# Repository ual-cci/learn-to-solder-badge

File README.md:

# Learn to Solder Badge

You can find out more about the CCI learn to solder baadge at [cci.to/badge](https://cci.to/badge).

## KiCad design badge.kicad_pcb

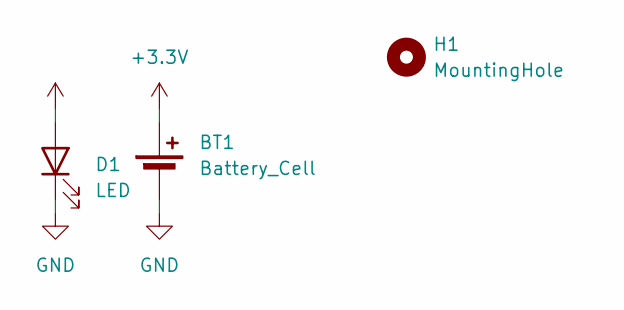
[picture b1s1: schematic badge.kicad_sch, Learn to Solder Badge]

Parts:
BT1: Battery_Cell; Clean CR2032 Holder Footprint
D1: LED; LED_D5.0mm
H1: MountingHole; MountingHole_2mm

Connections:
+3.3V: BT1.1 (+), D1.2 (A)
GND: BT1.2 (-), D1.1 (K)

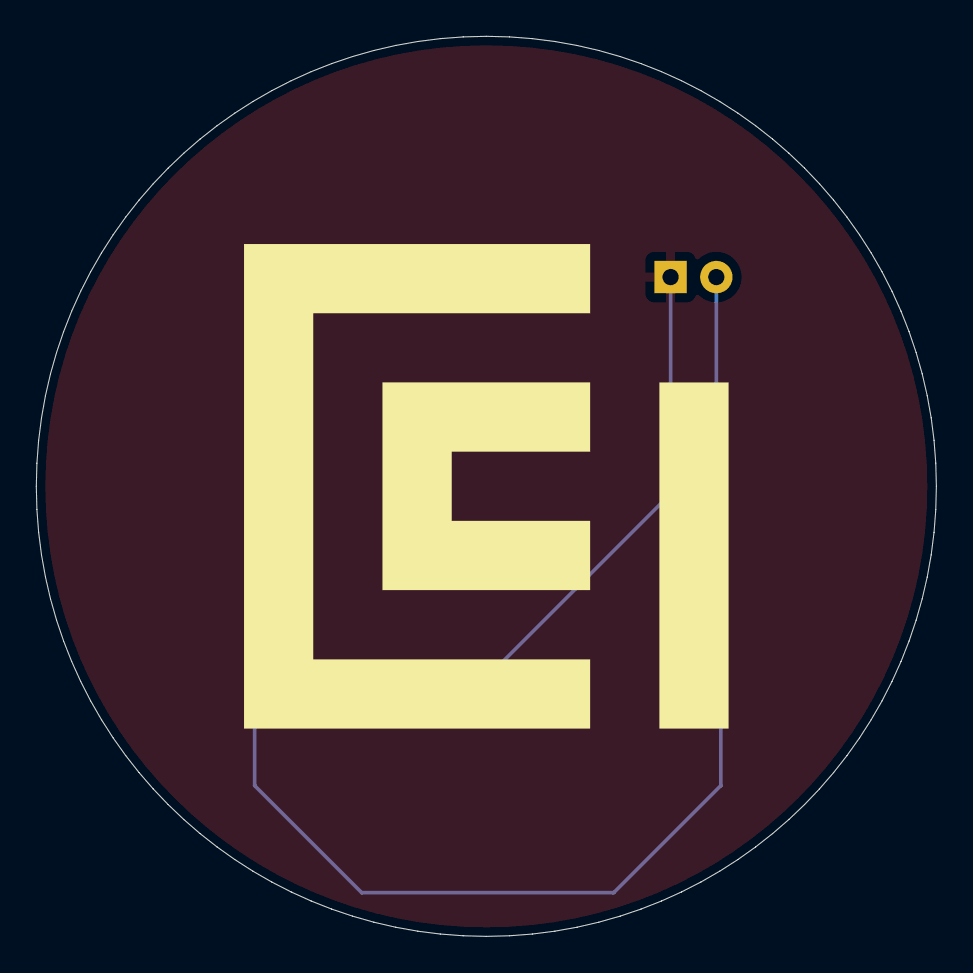
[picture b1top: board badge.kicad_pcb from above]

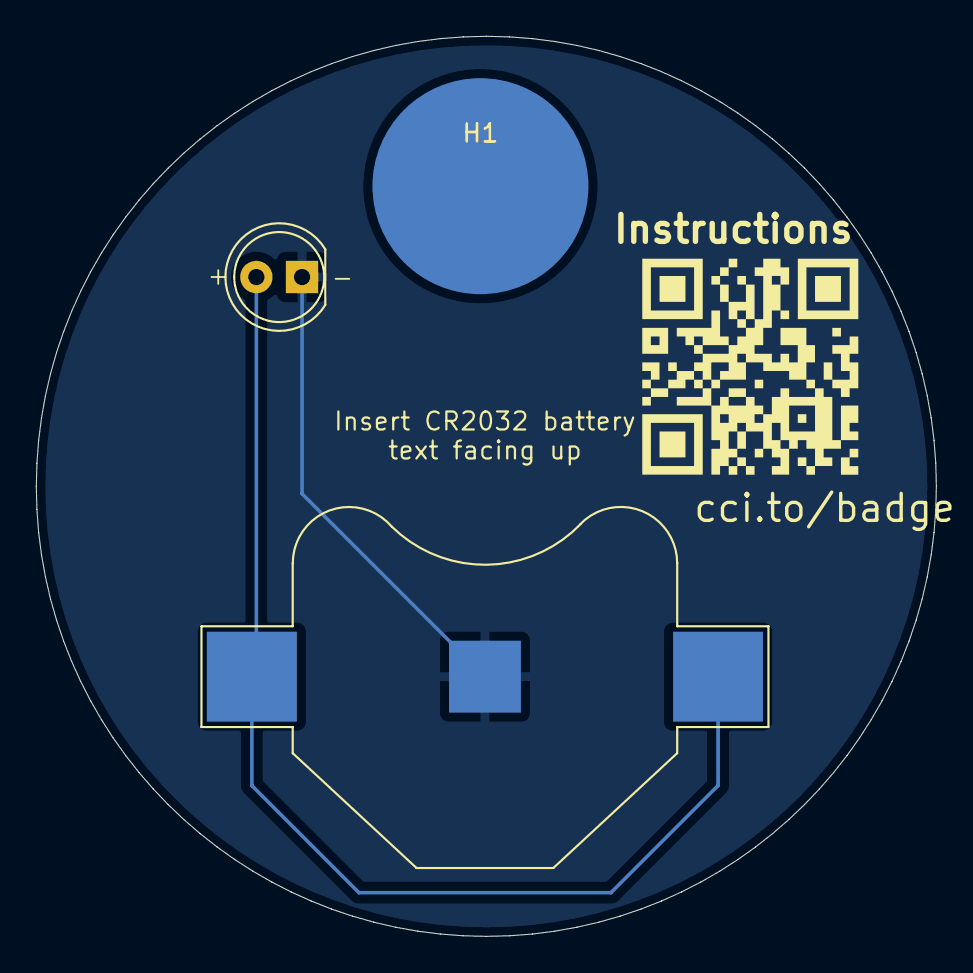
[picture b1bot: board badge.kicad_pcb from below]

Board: 2 copper layers, 50.0 x 50.0 mm, 3 parts (2 on the bottom side), 2 nets.

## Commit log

2025-08-21 Ignore macOS DS Store files
